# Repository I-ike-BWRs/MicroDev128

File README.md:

### *Thank You to PCBWay for sponsoring this project! To see more look up the "Sponsorship Section"*

---

# MicroDev128-32P
## A high-power development/prototyping board with MVIO. 

Based on the AVR128DB32. 

The MicroDev128-32P is open-source development board with a high-power voltage regulator with up to 2A continous, Multi-voltage IO - which allows PortC to run on a different voltage than the rest of the board - elimenating the need for voltage level shifters. The MicroDev128-32P aims to be better price to performance ratio than a tradition Arduino Nano. To view the Schematics you can go into the Kicad files folder. All files were made on KiCad 10.04 and should import without other dependencies. The 3D models are all included in the folder. 

**Key Specifications:**
- Up to 2A continuos on both power lines, 3.3v and 5v with up to 36VDC input
- Arduino Nano sized footprint, allowing it to easily be plugged into breadboards
- 128kB Flash, 16kB SRAM, and 512B
- Has with internal clock adjustable up to 24MHz max
- Built in TVS and 5A fuse
- UPDI Header for easy programing

## Documentation

For Documentation see the MicroDev128 Docs repository. 
[Link to Documents](https://github.com/ILikeBWRs/MicroDev128-Documentation)

---

## Images

---

## Sponsorship

[PCBWay](https://pcbway.com) is a professional manufacturing service that offers PCB fabrication, PCB assembly, CNC machining, sheet metal fabrication, injection molding, and high-quality 3D printing services. They support a wide range of materials, including stainless steel, aluminum, titanium, and engineering plastics, making them suitable for prototype and production projects.
For my project they gave me five indivdual PCBs of outstanding surface quality. They surface was flat and smooth - with a perfect ENIG coating - with the corners rounded and deburred. The end application of this project is a Microcontroller board, suitable to be used in many situations. To see how easy their ordering procsess is go to the ordering section. 

## Samples

A big thank you to the sample programs of the following manufactures:
 - Microchip Technology
 - Analog Devices
 - Coilcraft
 - Würth Elektronik

---

## Ordering

To order your own you have a few ways:

**1. Order PCBs and assemble them yourself**

*You will need a hotplate for solder reflow and solder paste. May be cheaper but harder to do!*

Upload the Gebers at:
/MicroDev128-32P Production Files
   /Gebers.zip
Go to PCBWay's online ordering page and upload the gebers. Make sure it says 4-layers. Set it to ENIG, and set the solder mask to any colour you want. The rest of the default settings will be fine. Hit order or add stencil if you need one. It's that easy!

Next in the same folder find the BOM.csv and order the parts from your favorite part distributor. 
To lay out components once they turn up you can use the KiCad PCB layout. A dedicated image for this step will come later.

**2. Use PCBWay's PCBA service and get them shipped assembled**

Upload the Gebers at:

/Production Files

   /Gebers.zip
   
Go to your PCB and upload the gebers. Make sure it says 4-layers. Set it to ENIG, and set the solder mask to any colour you want. The default settings will be fine.
Then upload the BOM.csv and CPL.csv to the page. Then check if they in stock. (You may need to pre-order some parts!)
The check component orientation - it has a tendency to flip the LT8653S by 90 degrees. 
Then pay and let PCBWay's professional automated factory ship them fully assembled, right to your door!

## For more check out my stardance project page: -[Stardance Hackclub](https://stardance.hackclub.com/projects/6131)

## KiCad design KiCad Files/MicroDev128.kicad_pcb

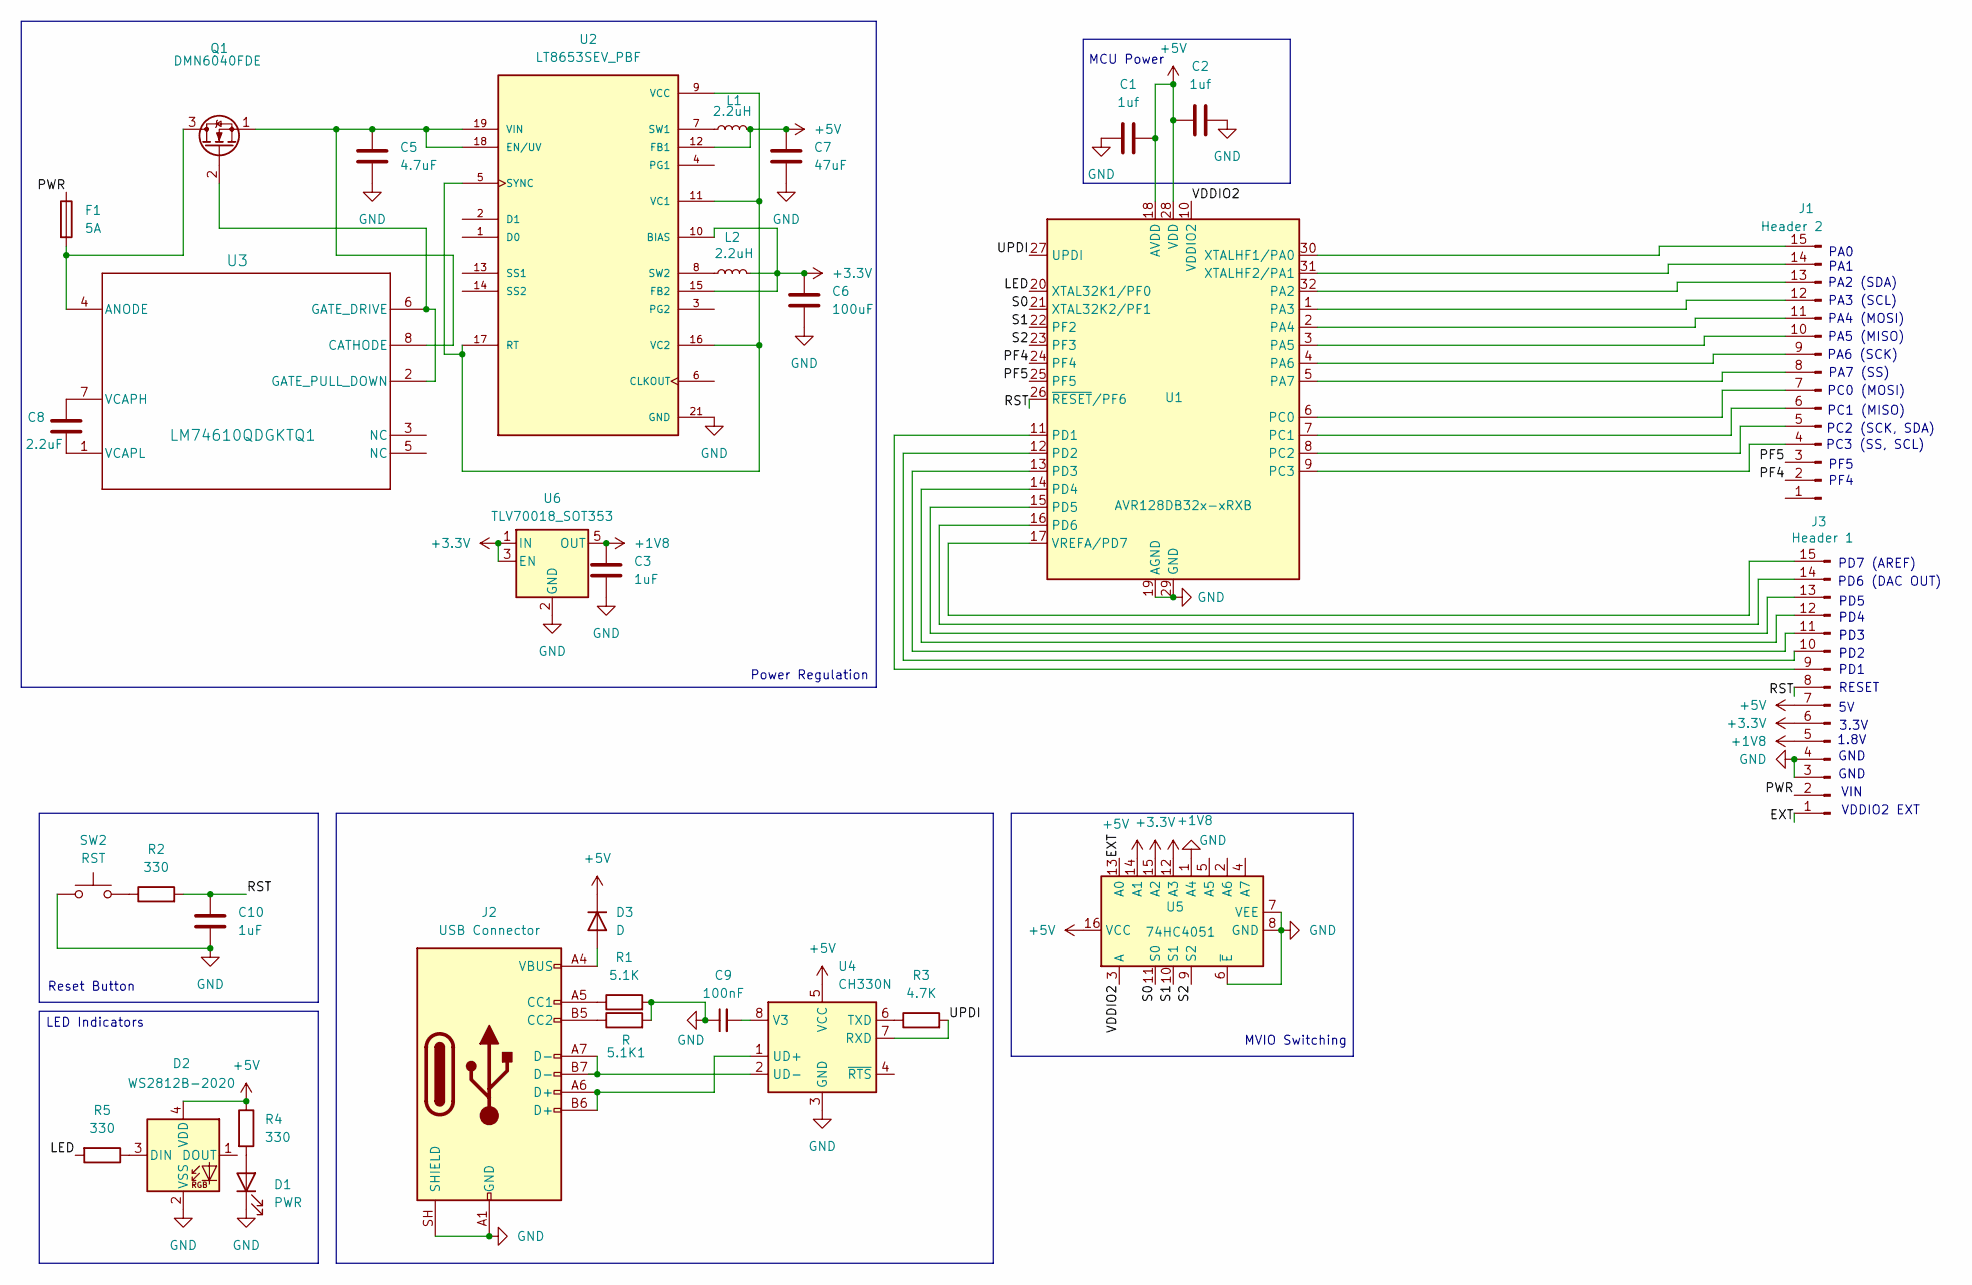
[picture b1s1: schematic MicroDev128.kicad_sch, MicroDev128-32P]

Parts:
5.1K1: R; R_0402_1005Metric
C1, C2: 1uf; C_0402_1005Metric
C3: 1uF; C_0402_1005Metric
C5: 4.7uF; C_1206_3216Metric
C6: 100uF; C_1206_3216Metric
C7: 47uF; C_1206_3216Metric
C8: 2.2uF; C_0402_1005Metric
C9: 100nF; C_0402_1005Metric
C10: 1uF; C_0603_1608Metric
D1: PWR; LED_0603_1608Metric
D2: WS2812B-2020; LED_WS2812B-2020_PLCC4_2.0x2.0mm
D3: D; D_SOD-323
F1: 5A; Fuse_0603_1608Metric
J1: Header 2; PinHeader_1x15_P2.54mm_Vertical
J2: USB Connector; USB_C_Receptacle_HRO_TYPE-C-31-M-12
J3: Header 1; PinHeader_1x15_P2.54mm_Vertical
L1, L2: 2.2uH; L_Taiyo-Yuden_NR-40xx
Q1: DMN6040FDE; DFN-6-1EP_2x2mm_P0.65mm_EP1.01x1.7mm
R1: 5.1K; R_0402_1005Metric
R2, R4, R5: 330; R_0402_1005Metric
R3: 4.7K; R_0402_1005Metric
SW2: RST; SW_Tactile_SPST_NO_Straight_CK_PTS636Sx25SMTRLFS
U1: AVR128DB32x-xRXB; QFN-32-1EP_5x5mm_P0.5mm_EP3.1x3.1mm
U2: LT8653SEV_PBF; QFN-20-1EP_3x4mm_P0.5mm_EP1.65x2.65mm; PARTREV B
U3: LM74610QDGKTQ1; VSSOP-8_3x3mm_P0.65mm
U4: CH330N; SOIC-8_3.9x4.9mm_P1.27mm
U5: 74HC4051; DHVQFN-16-1EP_2.5x3.5mm_P0.5mm_EP1x2mm
U6: TLV70018_SOT353; SOT-353_SC-70-5

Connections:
+1V8: C3.1, J3.5, U5.12 (A3), U6.5 (OUT)
+3.3V: C6.1, J3.6, L2.2, U2.10 (BIAS), U2.15 (FB2), U5.15 (A2), U6.1 (IN), U6.3 (EN)
+5V: C1.2, C2.1, C7.1, D2.4 (VDD), D3.1 (K), J3.7, L1.2, R4.1, U1.18 (AVDD), U1.28 (VDD), U2.12 (FB1), U4.5 (VCC), U5.14 (A1), U5.16 (VCC)
/EXT: J3.1, U5.13 (A0)
/LED: R5.2, U1.20 (XTAL32K1/PF0)
/PF4: J1.2, U1.24 (PF4)
/PF5: J1.3, U1.25 (PF5)
/PWR: F1.1, J3.2
/RST: C10.1, J3.8, R2.2, U1.26 (~RESET/PF6)
/S0: U1.21 (XTAL32K2/PF1), U5.11 (S0)
/S1: U1.22 (PF2), U5.10 (S1)
/S2: U1.23 (PF3), U5.9 (S2)
/UPDI: R3.2, U1.27 (UPDI), U4.7 (RXD)
/VDDIO2: U1.10 (VDDIO2), U5.3 (A)
GND: 5.1K1.2, C1.1, C2.2, C3.2, C5.2, C6.2, C7.2, C9.1, C10.2, D1.1 (K), D2.2 (VSS), J2.A1 (GND), J2.A12 (GND), J2.B1 (GND), J2.B12 (GND), J2.SH (SHIELD), J3.3, J3.4, R1.2, SW2.1, U1.19 (AGND), U1.29 (GND), U1.33 (GND), U2.21 (GND), U4.3 (GND), U5.1 (A4), U5.6 (~E), U5.7 (VEE), U5.8 (GND), U6.2 (GND)
unnamed: D1.2 (A), R4.2
unnamed: D2.3 (DIN), R5.1
unnamed: D3.2 (A), J2.A4 (VBUS), J2.A9 (VBUS), J2.B4 (VBUS), J2.B9 (VBUS)
unnamed: J1.4, U1.9 (PC3)
unnamed: J1.5, U1.8 (PC2)
unnamed: J1.6, U1.7 (PC1)
unnamed: J1.7, U1.6 (PC0)
unnamed: J1.8, U1.5 (PA7)
unnamed: J1.9, U1.4 (PA6)
unnamed: J1.10, U1.3 (PA5)
unnamed: J1.11, U1.2 (PA4)
unnamed: J1.12, U1.1 (PA3)
unnamed: J1.13, U1.32 (PA2)
unnamed: J1.14, U1.31 (XTALHF2/PA1)
unnamed: J1.15, U1.30 (XTALHF1/PA0)
unnamed: J2.A5 (CC1), R1.1
unnamed: 5.1K1.1, J2.B5 (CC2)
unnamed: J3.9, U1.11 (PD1)
unnamed: J3.10, U1.12 (PD2)
unnamed: J3.11, U1.13 (PD3)
unnamed: J3.12, U1.14 (PD4)
unnamed: J3.13, U1.15 (PD5)
unnamed: J3.14, U1.16 (PD6)
unnamed: J3.15, U1.17 (VREFA/PD7)
unnamed: F1.2, Q1.3 (D), U3.4 (ANODE)
unnamed: Q1.2 (G), U3.2 (GATE_PULL_DOWN), U3.6 (GATE_DRIVE)
unnamed: C5.1, Q1.1 (S), U2.18 (EN/UV), U2.19 (VIN), U2.20 (VIN), U3.8 (CATHODE)
unnamed: R2.1, SW2.2
unnamed: U2.5 (SYNC), U2.9 (VCC), U2.11 (VC1), U2.16 (VC2), U2.17 (RT)
unnamed: L1.1, U2.7 (SW1)
unnamed: L2.1, U2.8 (SW2)
unnamed: C8.1, U3.7 (VCAPH)
unnamed: C8.2, U3.1 (VCAPL)
unnamed: R3.1, U4.6 (TXD)
unnamed: J2.A6 (D+), J2.B6 (D+), U4.1 (UD+)
unnamed: J2.A7 (D-), J2.B7 (D-), U4.2 (UD-)
unnamed: C9.2, U4.8 (V3)

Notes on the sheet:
PD5
PC2 (SCK, SDA)
LED Indicators
GND
PA5 (MISO)
3.3V
PD3
Reset Button
PF4
PA7 (SS)
PC0 (MOSI)
PD2
VIN
PA1
PA0
PA4 (MOSI)
1.8V
RESET
PD6 (DAC OUT)
PF5
PA2 (SDA)
Power Regulation
PA6 (SCK)
PC1 (MISO)
MVIO Switching
VDDIO2 EXT
PD7 (AREF)
PA3 (SCL)
PD1
PC3 (SS, SCL)
PD4
MCU Power
GND

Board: 4 copper layers, 32 parts (2 on the bottom side), 52 nets, no tracks yet.

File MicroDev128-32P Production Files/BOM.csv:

"Reference","Value","Datasheet","Footprint","Qty","DNP"
"C1,C2,C3,C4","1uf","","Capacitor_SMD:C_0603_1608Metric","4",""
"C5","4.7uF","","Capacitor_SMD:C_1206_3216Metric","1",""
"C6","100uF","","Capacitor_SMD:C_1206_3216Metric","1",""
"C7","47uF","","Capacitor_SMD:C_1206_3216Metric","1",""
"C10","1uF","","Capacitor_SMD:C_0603_1608Metric","1",""
"D1","PWR","","LED_SMD:LED_0603_1608Metric","1",""
"D2","L","","LED_SMD:LED_0603_1608Metric","1",""
"D3","SMAJ36CA","","Diode_SMD:D_SMA","1",""
"F1","5A","","Fuse:Fuse_0603_1608Metric","1",""
"J1","UPDI Header","","Connector_PinHeader_2.54mm:PinHeader_2x03_P2.54mm_Vertical","1",""
"J3","GPIO","","Connector_PinHeader_2.54mm:PinHeader_1x14_P2.54mm_Vertical","1",""
"J4","PWR and ANALOG","","Connector_PinHeader_2.54mm:PinHeader_1x14_P2.54mm_Vertical","1",""
"L1,L2","2.2uH","","Inductor_SMD:L_Taiyo-Yuden_NR-40xx","2",""
"R2,R3,R4","330","","Resistor_SMD:R_0402_1005Metric","3",""
"SW1","SW_SP3T","","Button_Switch_SMD:SW_SP3T_PCM13","1",""
"SW2","RST","","Button_Switch_SMD:SW_Tactile_SPST_NO_Straight_CK_PTS636Sx25SMTRLFS","1",""
"U1","AVR128DB32x-xRXB","https://ww1.microchip.com/downloads/en/DeviceDoc/AVR128DB28-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","Package_DFN_QFN:QFN-32-1EP_5x5mm_P0.5mm_EP3.1x3.1mm","1",""
"U2","LT8653SEV_PBF","","Package_DFN_QFN:QFN-20-1EP_3x4mm_P0.5mm_EP1.65x2.65mm","1",""
